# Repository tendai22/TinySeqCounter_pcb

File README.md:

# TinyFreqCounter

A little 3 digit 7 segment LED display with a simple Frequency counter, for a companiou unit of retroPC SBC's.

可愛い3桁7セグメントLED表示器です。レトロCPU基板のCPUクロック周波数表示のために作りました。PIC18F27Q43のカウンタがいい感じで3種類あったので、外付けプリスケーラなしで1チップでできました。

3桁LEDディスプレイとPIC18Fの2チップ構成です。秋月C基板サイズ(72mm x 47mm)の上半分がLEDとPIC18Fチップで、下半分は蛇の目パターンにしてあります。簡単なセンサと組み合わせて無骨な温度計なんてのもありです。

レトロPCの外部クロック発生器を74HCU04と水晶でつくると、簡単な周波数カウンタとなります。

PICのファームウェアは https://github.com/tendai22/TinySeqCounter.git にあります。

## 周波数カウンタ

おおよそ100kHz～33MHzの範囲のクロックパルスを生成させ、CPUに食わせます。その時7セグLEDで周波数を表示させれば写真映えすると期待できます。

分解能として10進3桁、2進数で1024～2048の範囲の値を得て、そこから周波数3桁を定数を掛けたり割ったりして算出します。

周波数カウンタとしては、一定時間内のパルス数をカウントする方式です。測定時間は32.768msとします。を一定にしてプリスケーラを変えて測定終了し、結果を算出し表示します。1024～2048の範囲とは、10進数3桁に相当します。カウント後最下位ビットを見て「0捨1拾」して切りのいい数字にまとめます。

1MHz以上の範囲では、プリスケーラの分周数を次第に大きくしてオーバフローが収まり、カウント数が1024～2047の範囲になったところで測定終了、表示更新となります。

1MHz未満の範囲では、プリスケーラを1/1としてカウント数を32で割った値を周波数(kHz単位)とします。

## 7セグメントディスプレイ

なんの変哲もない素のダイナミック点灯です。1桁8msごとに更新して、ちらつきをなくしています。

## クロックジェネレータ

蛇の目部分に手配線で構成します。回路図と配線図は以下の通り。

<p style="text-align: center">
<br>
図1: クロックジェネレータ回路図<br>
<br>
図2: パターン配線図</p>

## 設計メモ

### 周波数カウンタ機能

まず、クロックパルスを数えるカウンタ、数える期間を算出するカウンタが必要になる。前者はTIM0, 後者をTIM1で行く。TIM0が持つ幅広い範囲のプリスケーラを活用することで、外付けプリスケーラが不要となった(4060を買っていたが)。

TIM1は測定期間を決めるタイマとして使う。Foscを4分周したものをTIM1に入れ、プリスケーラ1/8で16ビットカウンタとして使うと、16bitがあふれるまでの時間が32.768msとなり、これを測定期間とする。

入力クロックパルスの周波数をいくつか選び、分周比をいくらにすると32.768msの間に1024～2048パルスになるかを計算すると以下の表を得る。

|入力周波数|プリスケーラ<br>分周比|パルス幅|カウント|
|--:|--:|--:|--:|
|100MHz|1/2048|10.24us|1600|
|10MHz|1/256|25.6us|1280|
|1MHz|1/32|32us|1024|

100MHz～1MHzの範囲でプリスケーラを調整すると上の表を得る。
TIM0のプリスケーラ分周比は1/1から1/65536まで16段階で選べるので、この周波数範囲ならば10進数で有効数字3桁は問題なく確保できる。

1MHz～1kHzの範囲では、プリスケーラ分周比を1/1とする。すると、

|入力周波数|プリスケーラ<br>分周比|パルス幅|カウント|
|--:|--:|--:|--:|
|1000kHz|1/1|1us|32768|
|100kHz|1/1|10us|3276|
|10kHz|1/1|100us|327|
|1kHz|1/1|1000us|32|

となる。1kHz以下の精度は不要なので、この範囲では分周比1/1固定としてカウントを得ることにする。

### 7セグメントLEDダイナミック駆動

RC0-7をセグメントに割り当て、RB0-2を桁駆動に割り当てる。RC0-7側に電流制限抵抗(150ohmを選択)をつける。アノードコモン、カソードコモンどちらでもソフトで対応できると考える。

当初、周波数カウンタの測定期間32.768msを駆動周波数としてみたが、ちらつきが多く耐えられない。試行の結果、この1/4周期の8.192msでちらつきを抑えることができた。

TIM1を8.192msとして、4回ごとに測定を行うことにする。タイマがあと1つ(TIM2)使えるのでそれでダイナミック駆動することも考えたが、リフレッシュ処理の割り込みと測定周期が非同期となりはまり具合が予想できないので、リフレッシュ処理と測定のタイマを共通とし、一つの割り込み処理ルーチンの中で両処理を行うこととする。

### ピンアサイン

試作により周波数カウンタ機能とダイナミック駆動の処理を確認できたので、ピンアサインを確定させた。

|ピン|割り当て機能|説明|
|--|--|--|
|RB7,6|ICSPCLK,<br>ICSPDAT|これは固定で他の割り当てはできない。他との共用も避けた。|
|RB5,4|TX1,RX1|シリアルポートをここに割り当てる。
|RB3|T0CKI|クロックパルスをここに入力する。74HCU04による発振器だけでなく、SBCのPICが生成するクロックをここにつないでもよい。
|RB0-2|LED DIG1-3|7セグLEDのコモン端子3本を割り当てる
|RC0-7|LED A-F|7セグLEDのセグメント7個と小数点1個を割り当てる

PIC18Fのピン割り当ての柔軟さにより、RA0-7に手を付けずに周波数カウンタが実現できた。

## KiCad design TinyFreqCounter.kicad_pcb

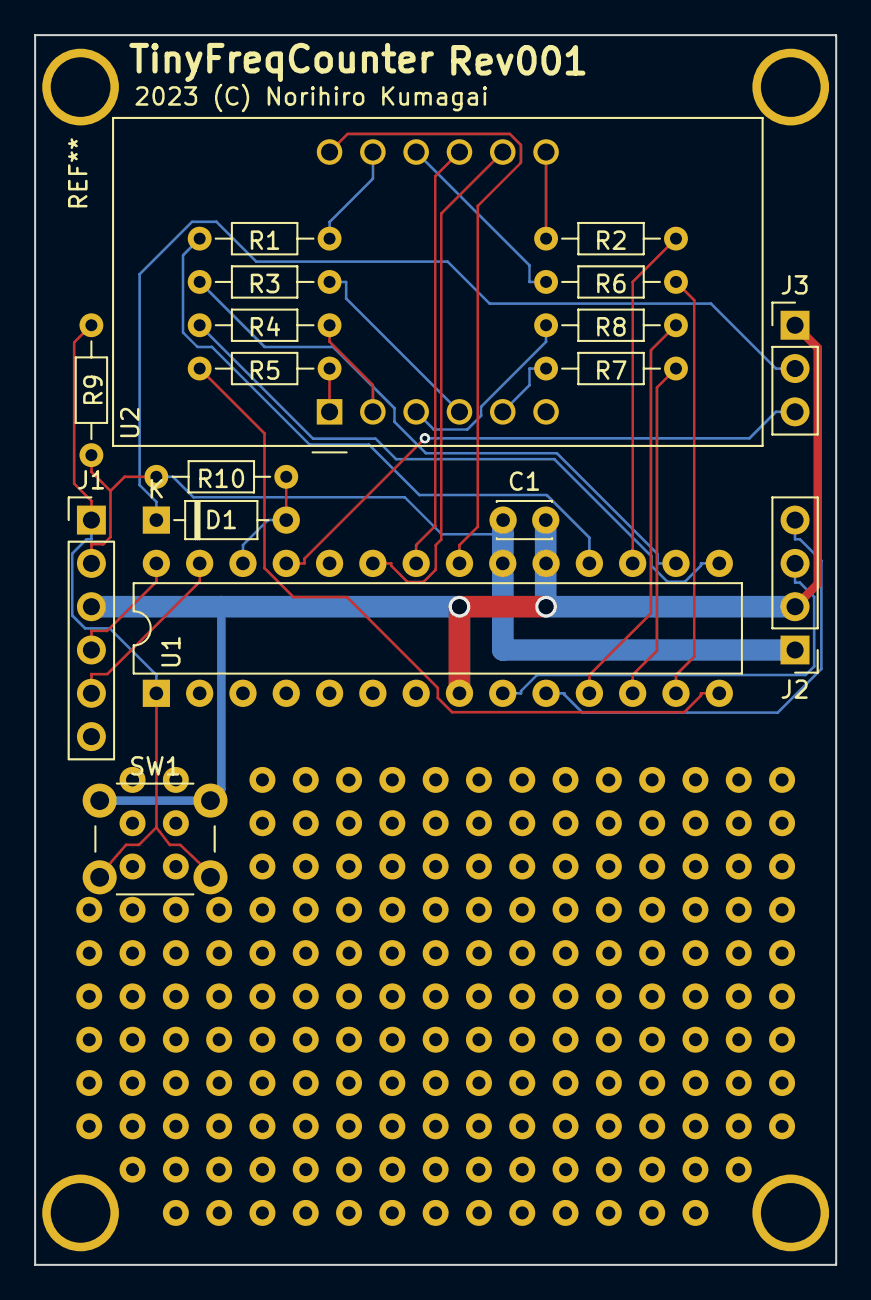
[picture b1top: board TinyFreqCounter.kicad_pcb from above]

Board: 2 copper layers, 47.0 x 72.1 mm, 18 parts (0 on the bottom side), 29 nets.

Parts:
C1: 0.1uF; C_Disc_D3.0mm_W2.0mm_P2.50mm
D1: 1N4148; D_DO-35_SOD27_P7.62mm_Horizontal
J1: SNAP; PinHeader_1x06_P2.54mm_Vertical
J2: CLKIO; PinHeader_1x04_P2.54mm_Vertical
J3: Serial; PinHeader_1x03_P2.54mm_Vertical
R1, R2, R3, R4, R5, R6, R7, R8: 150; R_Axial_DIN0204_L3.6mm_D1.6mm_P7.62mm_Horizontal
R9, R10: 10k; R_Axial_DIN0204_L3.6mm_D1.6mm_P7.62mm_Horizontal
SW1: SW_Push; SW_PUSH_6mm_H4.3mm
U1: PIC18F27Q43-IP; DIP-28_W7.62mm
U2: OSL-30561; OSL-30561_no_courtyard

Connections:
/RX1: J3.3, U1.25 (RB4)
/TX1: D1.2 (A), R10.1, U1.26 (RB5)
GND: C1.2, J1.3, J2.2, J3.1, SW1.1, U1.8 (VSS), U1.19 (VSS)
unnamed: D1.1 (K), J3.2
unnamed: J1.1, R9.1, SW1.2, U1.1 (~MCLR)
unnamed: J1.4, U1.28 (RB7/ICSPDAT)
unnamed: J1.5, U1.27 (RB6/ICPSCLK)
unnamed: J2.3, U1.9 (RA7)
unnamed: J2.4, U1.10 (RA6)
unnamed: U1.21 (RB0), U2.12 (DIG1)
unnamed: U1.22 (RB1), U2.9 (DIG2)
unnamed: U1.23 (RB2), U2.8 (DIG3)
unnamed: R8.1, U1.11 (RC0)
unnamed: R7.1, U1.12 (RC1)
unnamed: R6.1, U1.13 (RC2)
unnamed: R5.1, U1.14 (RC3)
unnamed: R4.1, U1.15 (RC4)
unnamed: R3.1, U1.16 (RC5)
unnamed: R2.1, U1.17 (RC6)
unnamed: R1.1, U1.18 (RC7)
unnamed: R8.2, U2.3 (DP)
unnamed: R1.2, U2.11 (a)
unnamed: R2.2, U2.7 (b)
unnamed: R3.2, U2.4 (c)
unnamed: R4.2, U2.2 (d)
unnamed: R5.2, U2.1 (e)
unnamed: R6.2, U2.10 (f)
unnamed: R7.2, U2.5 (g)
VCC: C1.1, J1.2, J2.1, R9.2, R10.2, U1.20 (VDD)

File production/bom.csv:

Designator,Footprint,Quantity,Value,LCSC Part #
C1,C_Disc_D3.0mm_W2.0mm_P2.50mm,1,0.1uF,
D1,D_DO-35_SOD27_P7.62mm_Horizontal,1,1N4148,
J1,PinHeader_1x06_P2.54mm_Vertical,1,SNAP,
J2,PinHeader_1x04_P2.54mm_Vertical,1,CLKIO,
J3,PinHeader_1x03_P2.54mm_Vertical,1,Serial,
"R1, R2, R3, R4, R5, R6, R7, R8",R_Axial_DIN0204_L3.6mm_D1.6mm_P7.62mm_Horizontal,8,150,
"R10, R9",R_Axial_DIN0204_L3.6mm_D1.6mm_P7.62mm_Horizontal,2,10k,
SW1,SW_PUSH_6mm_H4.3mm,1,SW_Push,
U1,DIP-28_W7.62mm,1,PIC18F27Q43-IP,
U2,OSL-30561_no_courtyard,1,OSL-30561,

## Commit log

2023-06-13 Write README.md
2023-06-13 Design memo in README.md
2023-06-13 Rev001: garber generated, and ordered to JLCPCB
